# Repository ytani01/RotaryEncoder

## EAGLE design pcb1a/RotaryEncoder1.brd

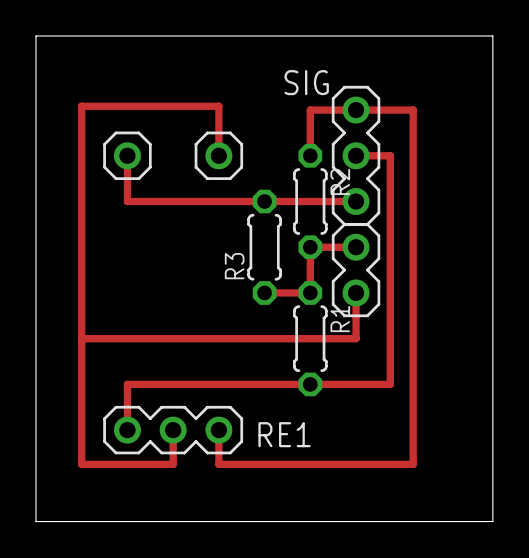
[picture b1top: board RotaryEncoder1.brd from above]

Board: 2 copper layers, 25.4 x 27.0 mm, 8 parts (0 on the bottom side), 5 nets.

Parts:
POW: PINHEAD-MA02-1
R1, R2, R3: 10K; 0204/5
RE1: PINHEAD-MA03-1
RE_G: PINHEAD-MA01-1
RE_SW: PINHEAD-MA01-1
SIG: PINHEAD-MA03-1

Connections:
+3V3: POW.1, R1.1, R2.2, R3.1
GND: POW.2, RE1.2, RE_G.1
unnamed: R3.2, RE_SW.1, SIG.3
unnamed: R1.2, RE1.3, SIG.2
unnamed: R2.1, RE1.1, SIG.1
